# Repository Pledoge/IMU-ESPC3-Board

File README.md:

# IMUMaster-PCB

## Project Overview
IMUMaster is a hardware circuit board project based on the **ICM-42688-P** (a high-precision 6-axis motion tracking/Inertial Measurement Unit). The schematic and PCB layout for this project are designed using **KiCad 9.0 (and above)**.
The board is equipped with an **ESP32-C3-WROOM-02** module for processing and communication, an **SY8120B** high-efficiency synchronous buck converter to provide stable power, and integrates an **MLT-9032** SMD buzzer for status indications or alarms. Power and programming can be achieved via the onboard USB-C receptacle or the JST single-row connector.

## Key Components
* **MCU/Wireless Module**: `ESP32-C3-WROOM-02` (Espressif) - Provides Wi-Fi & Bluetooth LE connectivity and acts as the main controller.
* **IMU Sensor**: `ICM-42688-P` (TDK InvenSense) - 6-axis motion tracking device (3-axis gyroscope + 3-axis accelerometer).
* **Power Management**: `SY8120B` (Silergy) - High-efficiency 2A, 18V input synchronous step-down regulator.
* **Audio Feedback**: `MLT-9032` - SMD passive/active buzzer.
* **Connectors**: 16-pin USB Type-C receptacle, JST XH 2.50mm 1x02 for external power input.

## Pin Configurations
Depending on the schematic routing, the key pinouts and interfaces are typically summarized as follows:
* **IMU (ICM-42688-P) Interface**: Connects to the ESP32-C3 via the SPI or I2C bus (Check the schematic for exact `SCL/SCLK`, `SDA/SDI`, `SDO`, `CS` pin mappings).
* **Buzzer (MLT-9032)**: Driven by an ESP32-C3 GPIO via a PWM signal to generate tones.
* **USB-C (16-Pin)**: Used for `VBUS` (Power input) and `D+/D-` for USB Serial / JTAG flashing for the ESP32-C3.
* **JST-XH (1x02)**: Used for external power supply input (e.g. Battery `VCC` and `GND`).

## Directory Structure
- `IMUMaster.kicad_sch` / `.kicad_pcb`: Core KiCad schematic and PCB design files. *(Requires KiCad 9.0 or later)*
- `kicad_api_libs/`: Contains project-specific component symbols (`.kicad_sym`), footprints (`.pretty`/`.kicad_mod`), and 3D models.
- `bom/`: Contains the interactive BOM file (`ibom.html`), which is highly recommended for manual soldering and debugging.
- `production/`: Manufacturing & fabrication files ready to be sent to PCBA manufacturers (like JLCPCB), including the production BOM (`bom.csv`) and component placement coordinates (`positions.csv`).

## Fabrication and PCBA Instructions
All necessary files for fabrication and PCB Assembly (PCBA) are located in the `production/` directory.
You can directly use the provided Bill of Materials (BOM) and CPL/POS data for manufacturing submission.

## Local Viewing and Editing
1. Please install [KiCad EDA](https://www.kicad.org/) **version 9.0 or newer**.
2. Double-click the `IMUMaster.kicad_pro` file to open the entire project, schematic, and PCB layout.
3. Open `bom/ibom.html` in your web browser to preview the Interactive BOM, which clearly highlights the exact position of each component on the PCB.
# IMU-ESPC3-Board

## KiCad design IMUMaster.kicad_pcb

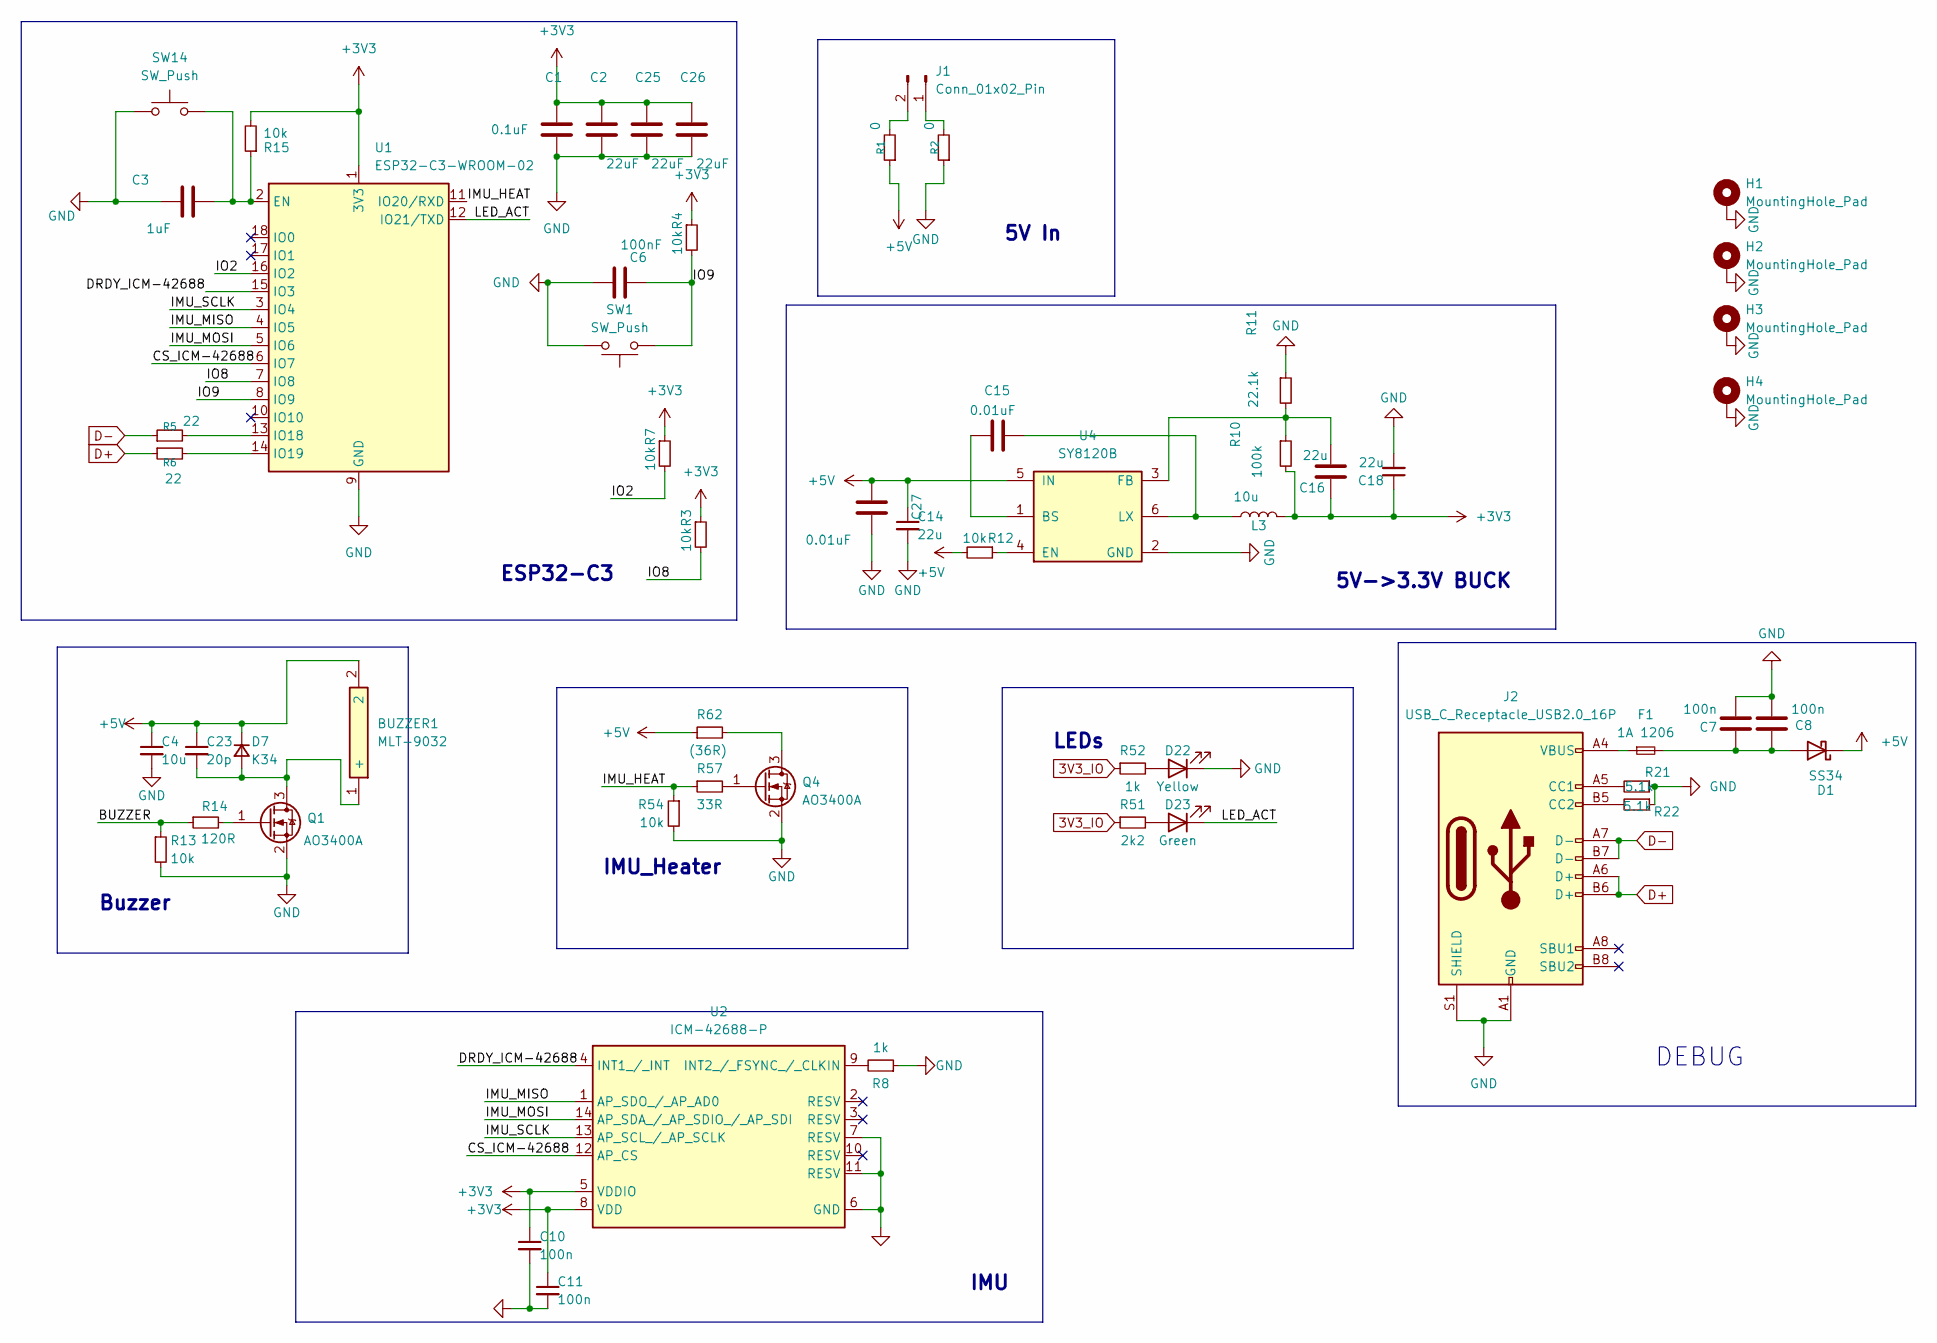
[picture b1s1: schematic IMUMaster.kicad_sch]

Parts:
BUZZER1: MLT-9032; voltage 2.5 V; voltage_rating 3.6 V; MPN MLT-9032
C1: 0.1uF; C_0603_1608Metric
C2, C25, C26: 22uF; C_1206_3216Metric
C3: 1uF; C_0603_1608Metric
C4: 10u; C_0603_1608Metric
C6: 100nF; C_0603_1608Metric
C7, C8, C10, C11: 100n; C_0603_1608Metric
C14, C16, C18: 22u; C_1206_3216Metric
C15, C27: 0.01uF; C_0603_1608Metric
C23: 20p; C_0603_1608Metric
D1: SS34; D_SMA
D7: K34; D_SMF
D22: Yellow; LED_0603_1608Metric
D23: Green; LED_0603_1608Metric
F1: 1A 1206; Fuse_1206_3216Metric
H1, H2, H3, H4: MountingHole_Pad; MountingHole_3.2mm_M3_DIN965_Pad
J1: Conn_01x02_Pin; JST_XH_B2B-XH-A_1x02_P2.50mm_Vertical
J2: USB_C_Receptacle_USB2.0_16P; USB_C_Receptacle_GCT_USB4105-xx-A_16P_TopMnt_Horizontal
L3: 10u; L_Vishay_IHLP-2020
Q1, Q4: AO3400A; SOT-23
R1, R2: 0; R_0603_1608Metric
R3, R4, R7, R12, R13, R15, R54: 10k; R_0603_1608Metric
R5, R6: 22; R_0603_1608Metric
R8, R52: 1k; R_0603_1608Metric
R10: 100k; R_0603_1608Metric
R11: 22.1k; R_0603_1608Metric
R14: 120R; R_0603_1608Metric
R21, R22: 5.1k; R_0603_1608Metric
R51: 2k2; R_0603_1608Metric
R57: 33R; R_0603_1608Metric
R62: (36R); R_1206_3216Metric
SW1, SW14: SW_Push; SW_SPST_B3U-1000P
U1: ESP32-C3-WROOM-02
U2: ICM-42688-P; MPN ICM-42688-P
U4: SY8120B; MPN SY8120B

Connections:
3V3_IO: R51.1, R52.1
+3V3: C1.1, C2.1, C10.1, C11.1, C16.2, C18.1, C25.1, C26.1, L3.2, R3.1, R4.1, R7.1, R10.2, R15.2, U1.1 (3V3), U2.5 (VDDIO), U2.8 (VDD)
+5V: BUZZER1.2, C4.1, C14.1, C23.1, C27.2, D1.1 (K), D7.1 (K), R1.1, R12.2, R62.1, U4.5 (IN)
/BUZZER: R13.1, R14.1
/CS_ICM-42688: U1.6 (IO7), U2.12 (AP_CS)
/DRDY_ICM-42688: U1.15 (IO3), U2.4 (INT1_/_INT)
/IMU_HEAT: R54.1, R57.1, U1.11 (IO20/RXD)
/IMU_MISO: U1.4 (IO5), U2.1 (AP_SDO_/_AP_AD0)
/IMU_MOSI: U1.5 (IO6), U2.14 (AP_SDA_/_AP_SDIO_/_AP_SDI)
/IMU_SCLK: U1.3 (IO4), U2.13 (AP_SCL_/_AP_SCLK)
/IO2: R7.2, U1.16 (IO2)
/IO8: R3.2, U1.7 (IO8)
/IO9: C6.1, R4.2, SW1.1, U1.8 (IO9)
/LED_ACT: D23.1 (K), U1.12 (IO21/TXD)
D+: J2.A6 (D+), J2.B6 (D+), R6.1
D-: J2.A7 (D-), J2.B7 (D-), R5.1
GND: C1.2, C2.2, C3.1, C4.2, C6.2, C7.2, C8.2, C10.2, C11.2, C14.2, C18.2, C25.2, C26.2, C27.1, D22.1 (K), H1.1, H2.1, H3.1, H4.1, J2.A1 (GND), J2.A12 (GND), J2.B1 (GND), J2.B12 (GND), J2.S1 (SHIELD), Q1.2 (S), Q4.2 (S), R2.1, R8.1, R11.1, R13.2, R21.1, R22.1, R54.2, SW1.2, SW14.1, U1.9 (GND), U1.19 (GND), U2.6 (GND), U2.7 (RESV), U2.11 (RESV), U4.2 (GND)
unnamed: BUZZER1.1 (+), C23.2, D7.2 (A), Q1.3 (D)
unnamed: C7.1, C8.1, D1.2 (A), F1.2
unnamed: D22.2 (A), R52.2
unnamed: D23.2 (A), R51.2
unnamed: F1.1, J2.A4 (VBUS), J2.A9 (VBUS), J2.B4 (VBUS), J2.B9 (VBUS)
unnamed: J1.1, R2.2
unnamed: J1.2, R1.2
unnamed: J2.A5 (CC1), R21.2
unnamed: J2.B5 (CC2), R22.2
unnamed: Q1.1 (G), R14.2
unnamed: Q4.3 (D), R62.2
unnamed: Q4.1 (G), R57.2
unnamed: C3.2, R15.1, SW14.2, U1.2 (EN)
unnamed: R5.2, U1.13 (IO18)
unnamed: R6.2, U1.14 (IO19)
unnamed: R8.2, U2.9 (INT2_/_FSYNC_/_CLKIN)
unnamed: C15.2, U4.1 (BS)
unnamed: R12.1, U4.4 (EN)
unnamed: C16.1, R10.1, R11.2, U4.3 (FB)
unnamed: C15.1, L3.1, U4.6 (LX)

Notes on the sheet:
LEDs
5V In
IMU_Heater
Buzzer
DEBUG
IMU
5V->3.3V BUCK
ESP32-C3

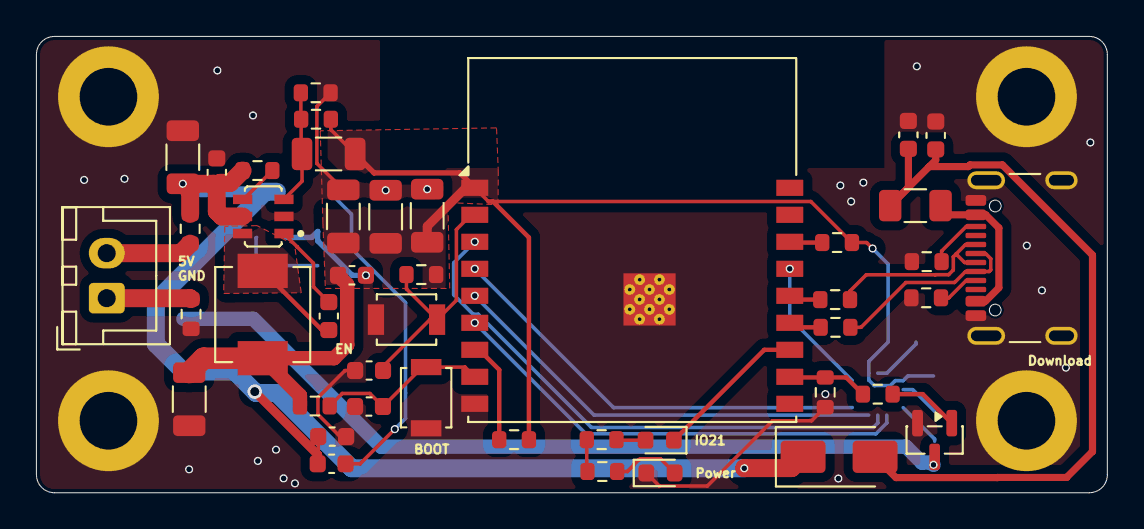
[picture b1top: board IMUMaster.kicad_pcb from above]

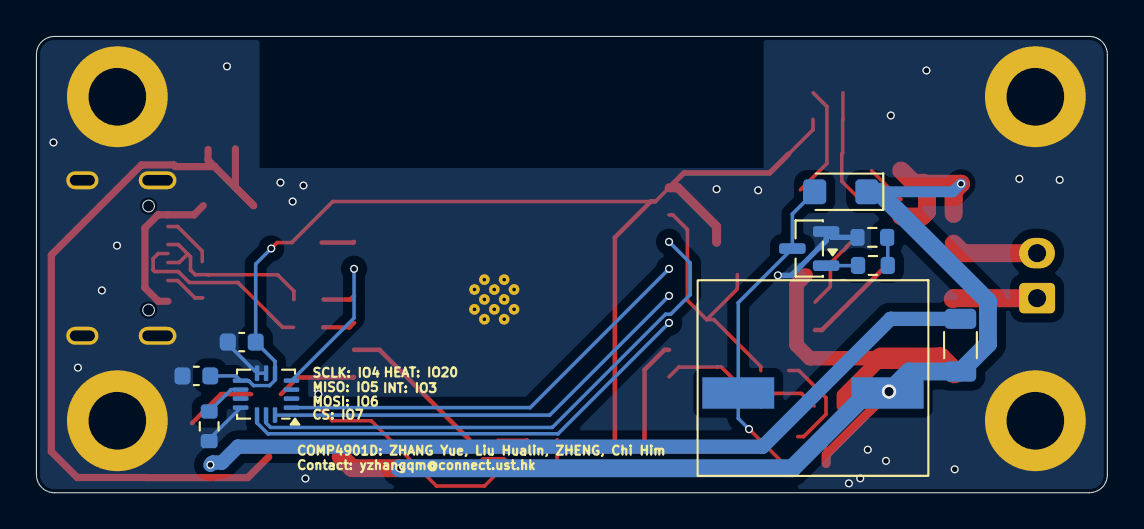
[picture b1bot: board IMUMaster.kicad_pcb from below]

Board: 2 copper layers, 59.5 x 25.3 mm, 58 parts (10 on the bottom side), 37 nets.

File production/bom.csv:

Designator,Footprint,Quantity,Value,LCSC Part #
BUZZER1,MLT-9032,1,MLT-9032,MLT-9032
C1,0603,1,0.1uF,
"C10, C11, C7, C8",0603,4,100n,
"C14, C16, C18",1206,3,22u,
"C15, C27",0603,2,0.01uF,
"C2, C25, C26",1206,3,22uF,
C23,0603,1,20p,
C3,0603,1,1uF,
C4,0603,1,10u,
C6,0603,1,100nF,
D1,D_SMA,1,SS34,
D22,0603,1,Yellow,
D23,0603,1,Green,
D7,D_SMF,1,K34,
F1,1206,1,1A 1206,
J1,JST_XH_B2B-XH-A_1x02_P2.50mm_Vertical,1,Conn_01x02_Pin,
J2,USB_C_Receptacle_GCT_USB4105-xx-A_16P_TopMnt_Horizontal,1,USB_C_Receptacle_USB2.0_16P,
L3,L_Vishay_IHLP-2020,1,10u,
"Q1, Q4",SOT-23,2,AO3400A,
"R1, R2",0603,2,0,
R10,0603,1,100k,
R11,0603,1,22.1k,
"R12, R13, R15, R3, R4, R54, R7",0603,7,10k,
R14,0603,1,120R,
"R21, R22",0603,2,5.1k,
"R5, R6",0603,2,22,
R51,0603,1,2k2,
"R52, R8",0603,2,1k,
R57,0603,1,33R,
R62,1206,1,(36R),
"SW1, SW14",SW_SPST_B3U-1000P,2,SW_Push,
U1,ESP32-C3-WROOM-02,1,ESP32-C3-WROOM-02,
U2,ICM-42688-P,1,ICM-42688-P,ICM-42688-P
U4,SY8120B,1,SY8120B,SY8120B

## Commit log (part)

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2026-05-09 change readme
